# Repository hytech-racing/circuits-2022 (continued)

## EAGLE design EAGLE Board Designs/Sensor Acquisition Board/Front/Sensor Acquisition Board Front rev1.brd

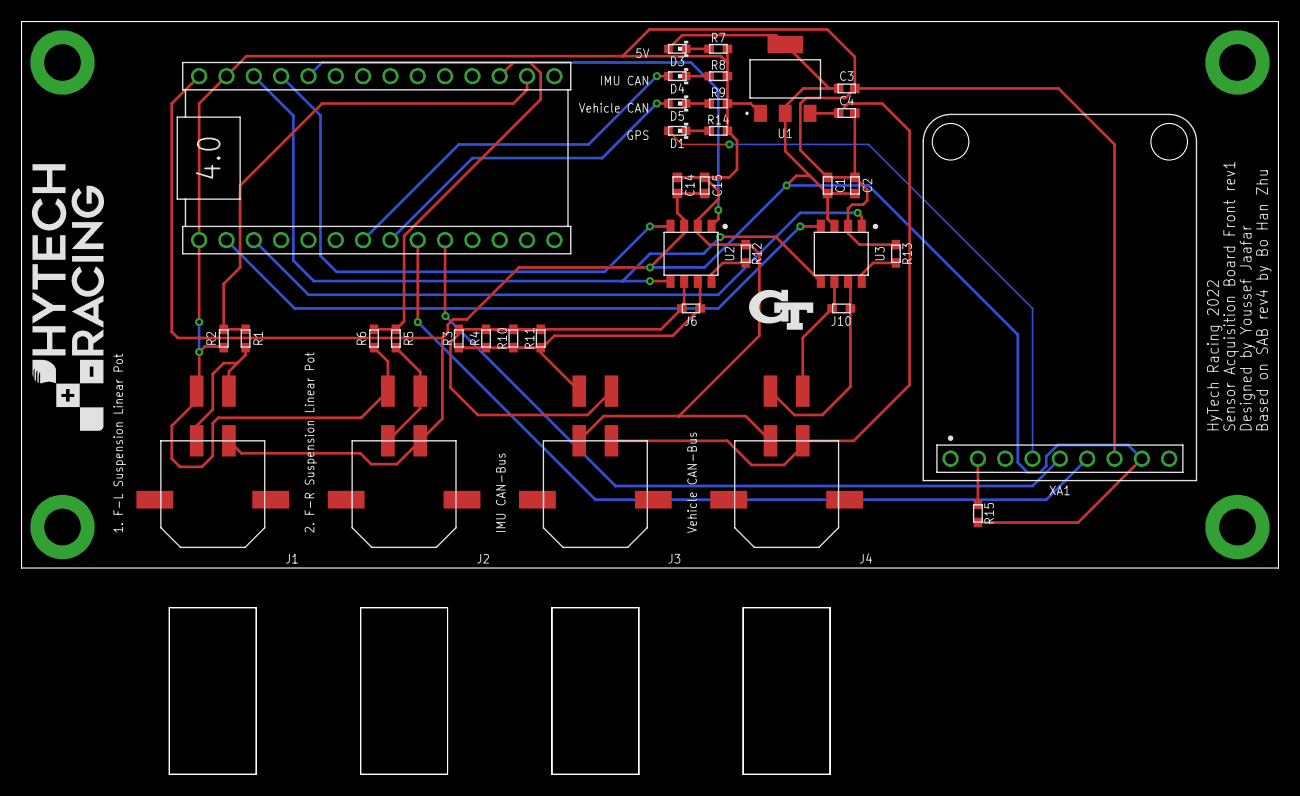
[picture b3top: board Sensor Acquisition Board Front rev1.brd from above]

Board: 2 copper layers, 116.8 x 50.8 mm, 42 parts (0 on the bottom side), 28 nets.

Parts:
A2: TEENSY_4.0; TEENSY_SHORT
C1, C15: CAPACITOR_0603_10V_0.1UF; 0603-CAP
C2, C14: CAPACITOR_0603_10V_1UF; 0603-CAP
C3: CAPACITOR_0603_10V_4.7UF; 0603-CAP
C4: CAPACITOR_0603_25V_1UF; 0603-CAP
D1, D3, D4, D5: LED_0603_RED; 0603-LED
J1, J2: CONNECTOR-4_μF_S_RA_; MOLEX_MICROFIT_SMD_RIGHTANGLE_04_DUAL
J3, J4: CONNECTOR-CAN_μF_S_RA_; MOLEX_MICROFIT_SMD_RIGHTANGLE_04_DUAL
J6, J10: JUMPER_0603_; 0603-RES
R1, R5, R12, R13, R15: RESISTOR_0603_10K; 0603-RES
R2, R6: RESISTOR_0603_12K; 0603-RES
R3, R4, R10, R11: RESISTOR_0603_240; 0603-RES
R7: RESISTOR_0603_1K; 0603-RES
R8, R9, R14: RESISTOR_0603_470; 0603-RES
U1: VOLTAGE_REGULATOR_SOT-223_5V; SOT-223
U2, U3: MCP2562FD; SOIC-08(NARROW,0.15")
U$1, U$2, U$4, U$5: MOUNTING_M3
U$6: LOGO_GT_0.25"
U$7: LOGO_HYTECH_MEDIUM
XA1: ULTIMATE_GPS

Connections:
+5V: A2.VIN, C1.2, C2.2, C3.1, C14.2, C15.2, D3.2, J1.1, J2.1, R15.2, U1.2, U1.4, U2.3, U3.3, XA1.VIN
+12V: C4.1, J3.1, J4.1, U1.3
CAN1_LED: A2.D5, D4.2
CAN2_LED: A2.D6, D5.2
CANH: J4.4, J10.1, U3.7
CANH1: J3.4, J6.1, R3.1, R4.1, R10.1, R11.1, U2.7
CANL: J4.3, J10.2, U3.6
CANL1: J3.3, J6.2, R3.2, R4.2, R10.2, R11.2, U2.6
CANRX1: A2.D23, U2.4
CANRX2: A2.D0, U3.4
CANTX1: A2.D22, U2.1
CANTX2: A2.D1, U3.1
GND: A2.AGND/GND, A2.GND, C1.1, C2.1, C3.2, C4.2, C14.1, C15.1, J1.4, J2.4, J3.2, J4.2, R2.1, R6.1, R7.2, R8.2, R9.2, R12.1, R13.1, R14.2, U1.1, U2.2, U3.2, XA1.GND
GPS_LED: D1.2, XA1.FIX
GPS_RX: A2.D7, XA1.RX
GPS_TX: A2.D8, XA1.TX
unnamed: R12.2, U2.8
unnamed: R13.2, U3.8
unnamed: D3.1, R7.1
unnamed: D1.1, R14.1
unnamed: D4.1, R8.1
unnamed: D5.1, R9.1
unnamed: R15.1, XA1.EN
unnamed: J1.2, J1.3, R1.2
unnamed: J2.2, J2.3, R5.2
SENSOR_1: A2.D14, R1.1, R2.2
SENSOR_2: A2.D15, R5.1, R6.2
TEENSY_3.3V: A2.3.3V, U2.5, U3.5

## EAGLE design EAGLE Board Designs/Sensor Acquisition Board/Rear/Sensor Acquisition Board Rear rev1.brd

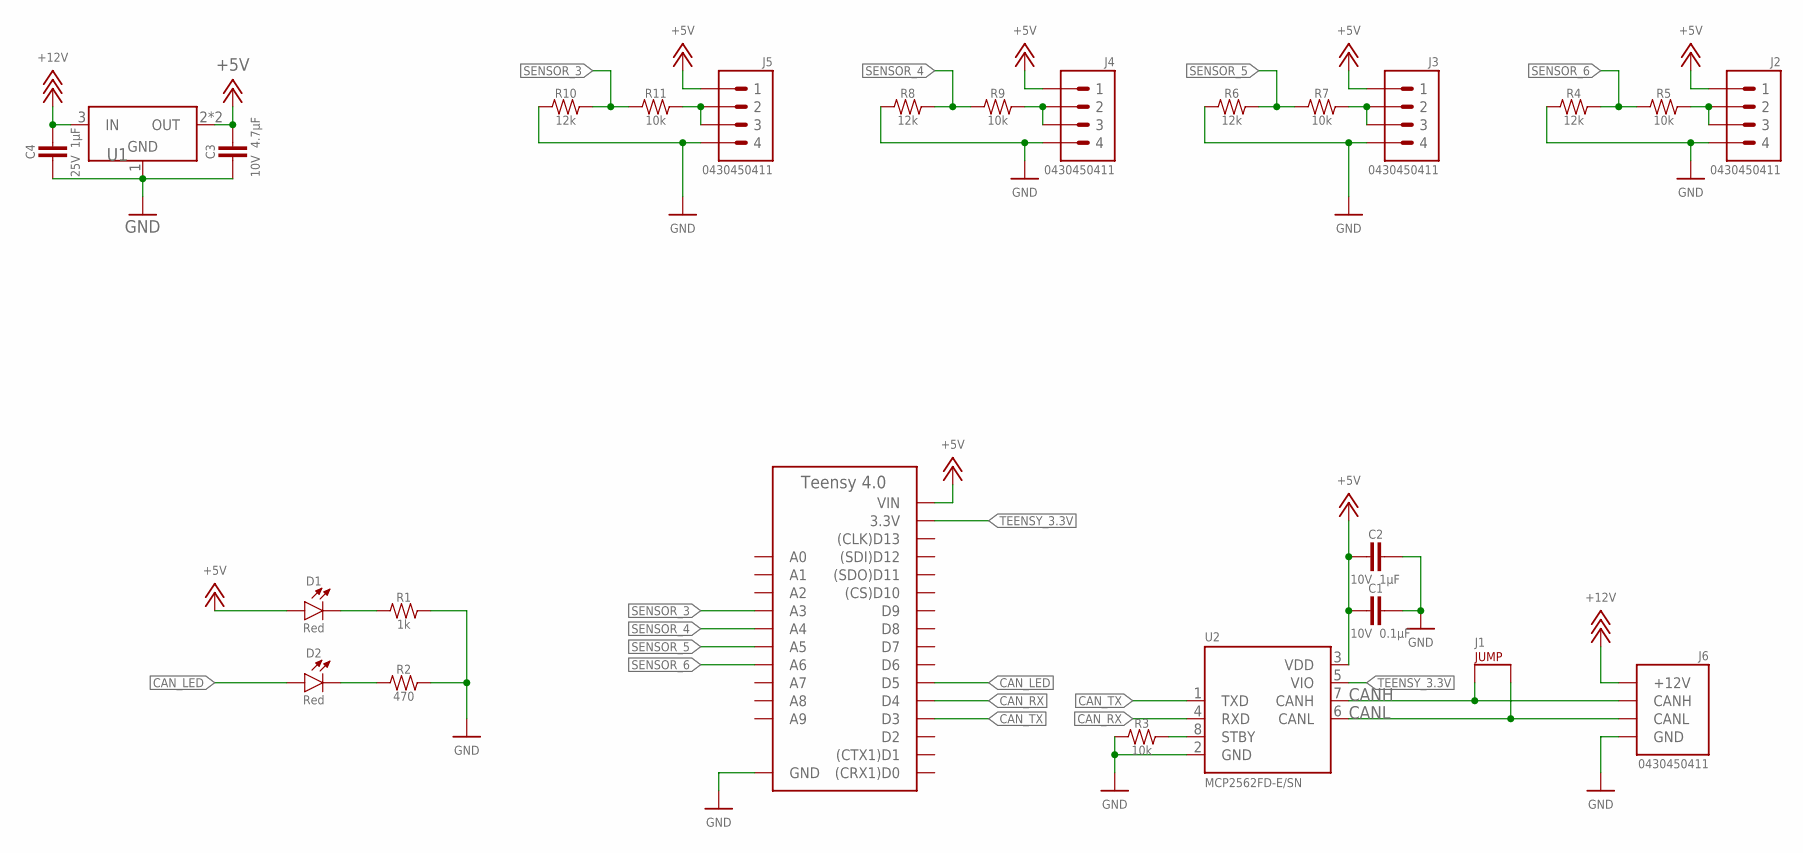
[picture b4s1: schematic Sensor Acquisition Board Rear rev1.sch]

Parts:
A1: TEENSY_4.0; TEENSY_SHORT
C1: CAPACITOR_0603_10V_0.1UF; 0603-CAP
C2: CAPACITOR_0603_10V_1UF; 0603-CAP
C3: CAPACITOR_0603_10V_4.7UF; 0603-CAP
C4: CAPACITOR_0603_25V_1UF; 0603-CAP
D1, D2: LED_0603_RED; 0603-LED
J1: JUMPER_0603_; 0603-RES
J2, J3, J4, J5: CONNECTOR-4_μF_S_RA_; MOLEX_MICROFIT_SMD_RIGHTANGLE_04_DUAL
J6: CONNECTOR-CAN_μF_S_RA_; MOLEX_MICROFIT_SMD_RIGHTANGLE_04_DUAL
R1: RESISTOR_0603_1K; 0603-RES
R2: RESISTOR_0603_470; 0603-RES
R3, R5, R7, R9, R11: RESISTOR_0603_10K; 0603-RES
R4, R6, R8, R10: RESISTOR_0603_12K; 0603-RES
U1: VOLTAGE_REGULATOR_SOT-223_5V; SOT-223
U2: MCP2562FD; SOIC-08(NARROW,0.15")

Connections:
+5V: A1.VIN, C1.2, C2.2, C3.1, D1.2 (A), J2.1, J3.1, J4.1, J5.1, U1.2 (OUT), U1.4 (OUT), U2.3 (VDD)
+12V: C4.1, J6.1 (+12V), U1.3 (IN)
CANH: J1.1, J6.4 (CANH), U2.7 (CANH)
CANL: J1.2, J6.3 (CANL), U2.6 (CANL)
CAN_LED: A1.D5, D2.2 (A)
CAN_RX: A1.D4, U2.4 (RXD)
CAN_TX: A1.D3, U2.1 (TXD)
unnamed: D1.1 (C), R1.1
unnamed: D2.1 (C), R2.1
unnamed: R3.2, U2.8 (STBY)
unnamed: J2.2, J2.3, R5.2
unnamed: J4.2, J4.3, R9.2
unnamed: J3.2, J3.3, R7.2
unnamed: J5.2, J5.3, R11.2
SENSOR_3: A1.D17 (A3), R10.2, R11.1
SENSOR_4: A1.D18 (A4), R8.2, R9.1
SENSOR_5: A1.D19 (A5), R6.2, R7.1
SENSOR_6: A1.D20 (A6), R4.2, R5.1
TEENSY_3.3V: A1.3.3V, U2.5 (VIO)

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
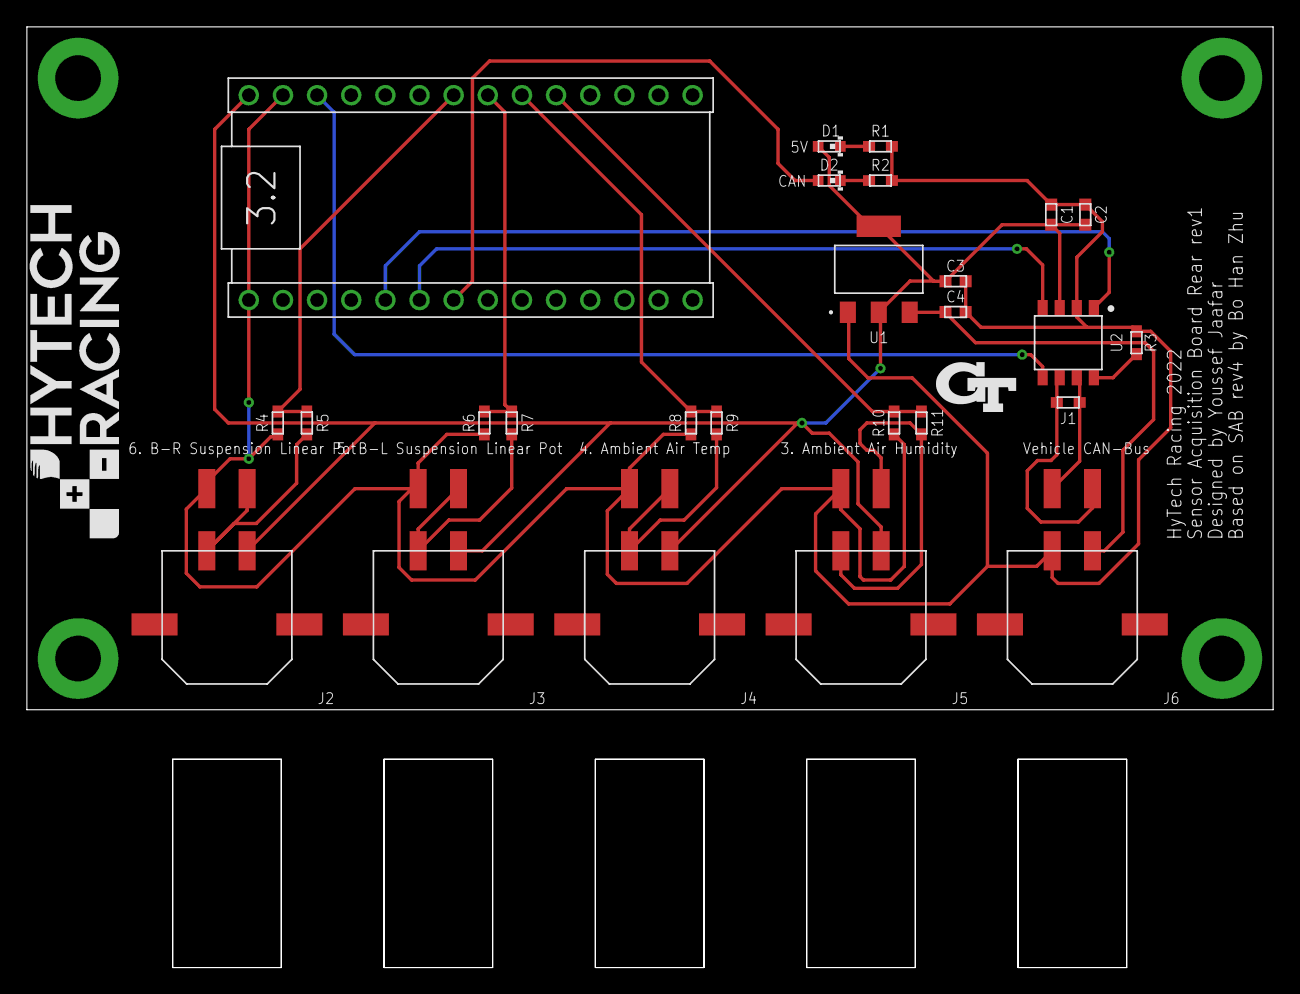
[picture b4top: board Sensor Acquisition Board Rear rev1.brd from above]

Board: 2 copper layers, 92.7 x 50.8 mm, 32 parts (0 on the bottom side), 20 nets.

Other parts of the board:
$$U$6: MOUNTING_M3
U$1, U$2, U$5: MOUNTING_M3
U$3: LOGO_GT_0.25"
U$4: LOGO_HYTECH_MEDIUM

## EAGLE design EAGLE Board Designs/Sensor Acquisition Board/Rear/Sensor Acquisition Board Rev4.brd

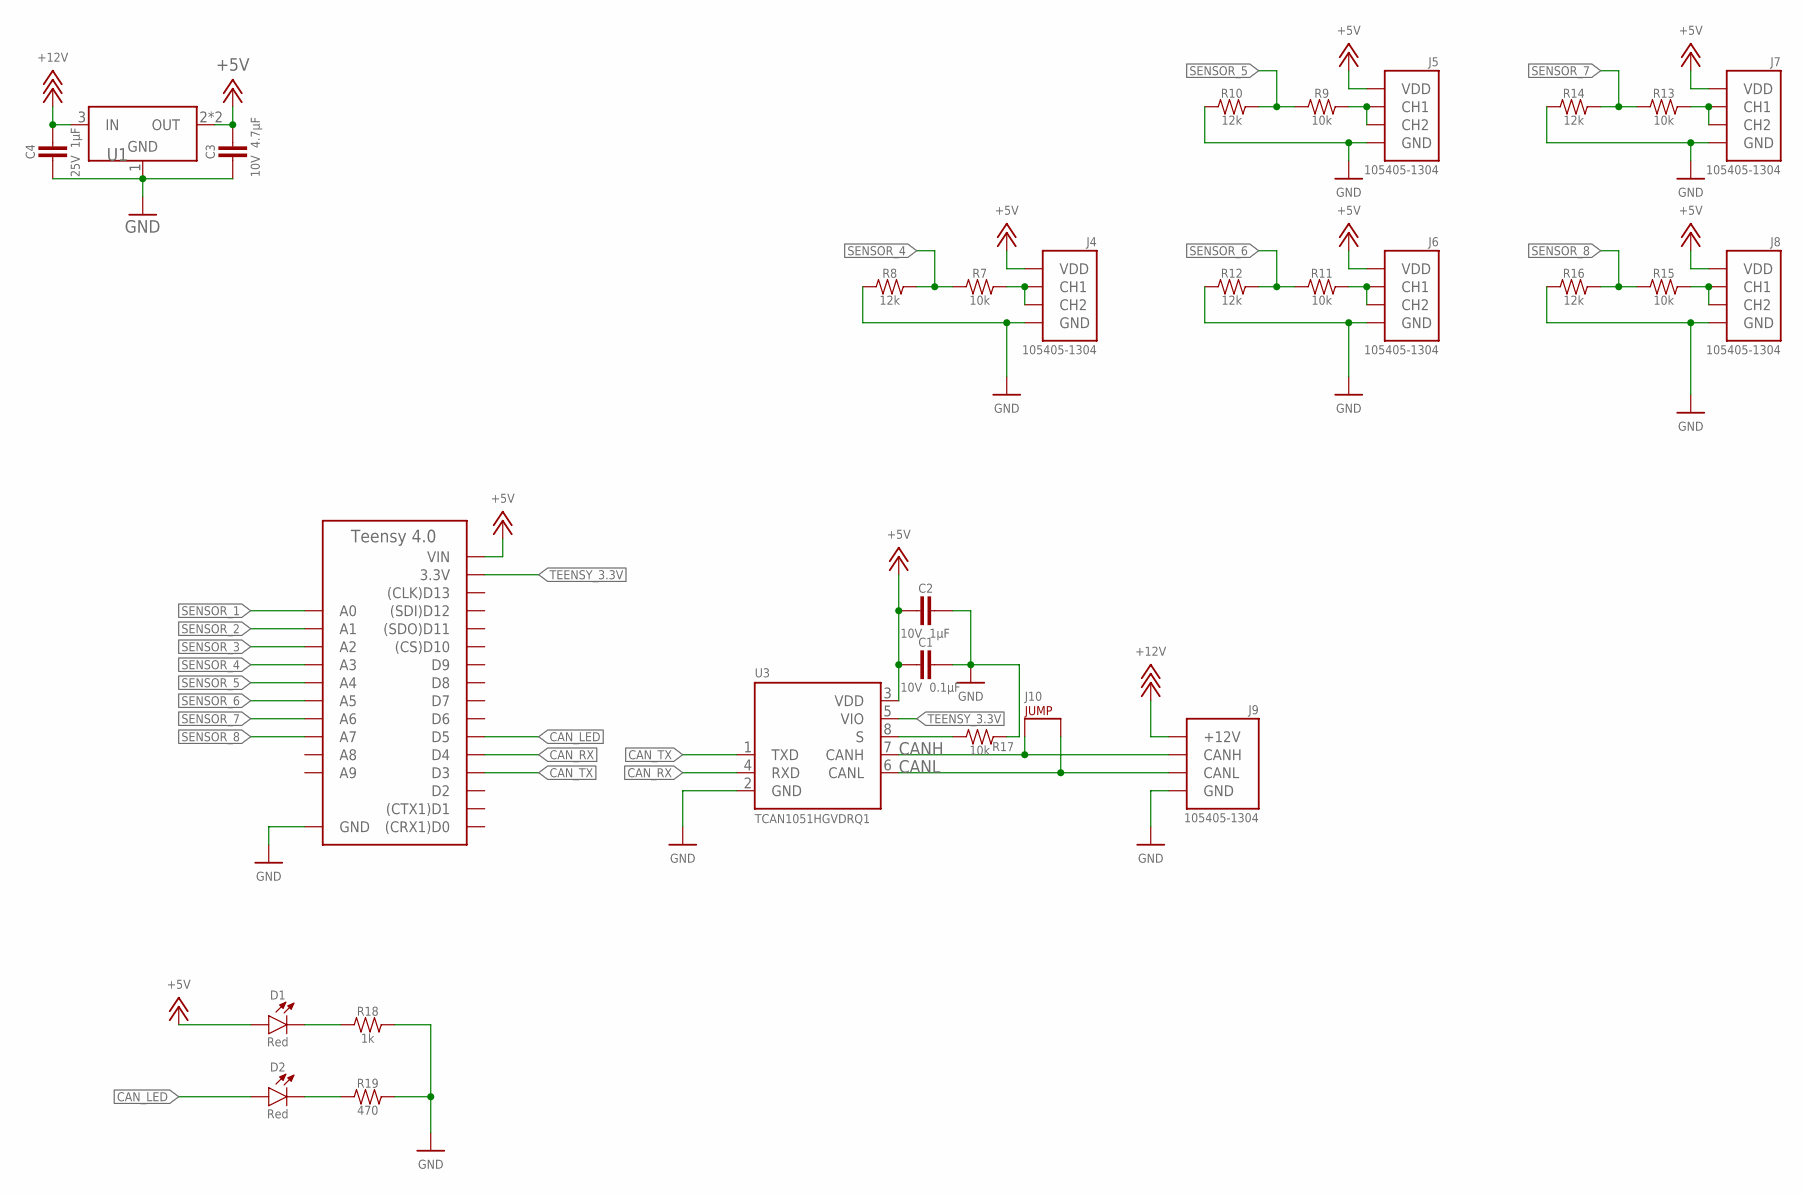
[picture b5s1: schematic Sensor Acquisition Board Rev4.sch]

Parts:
A2: TEENSY_4.0; TEENSY_SHORT
C1: CAPACITOR_0603_10V_0.1UF; 0603-CAP
C2: CAPACITOR_0603_10V_1UF; 0603-CAP
C3: CAPACITOR_0603_10V_4.7UF; 0603-CAP
C4: CAPACITOR_0603_25V_1UF; 0603-CAP
D1, D2: LED_0603_RED; 0603-LED
J4, J5, J6, J7, J8: CONNECTOR-SENSOR_NF_S_RA_BLACK; MOLEX_NANOFIT_SMD_RIGHTANGLE_04
J9: CONNECTOR-CAN_NF_S_RA_BLACK; MOLEX_NANOFIT_SMD_RIGHTANGLE_04
J10: JUMPER_0603_; 0603-RES
R7, R9, R11, R13, R15, R17: RESISTOR_0603_10K; 0603-RES
R8, R10, R12, R14, R16: RESISTOR_0603_12K; 0603-RES
R18: RESISTOR_0603_1K; 0603-RES
R19: RESISTOR_0603_470; 0603-RES
U1: VOLTAGE_REGULATOR_SOT-223_5V; SOT-223
U3: TCAN1051HQV-Q1; SOIC-08(NARROW,0.15")

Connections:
+5V: A2.VIN, C1.2, C2.2, C3.1, D1.2 (A), J4.1 (VDD), J5.1 (VDD), J6.1 (VDD), J7.1 (VDD), J8.1 (VDD), U1.2 (OUT), U1.4 (OUT), U3.3 (VDD)
+12V: C4.1, J9.1 (+12V), U1.3 (IN)
CANH: J9.4 (CANH), J10.1, U3.7 (CANH)
CANL: J9.3 (CANL), J10.2, U3.6 (CANL)
CAN_LED: A2.D5, D2.2 (A)
CAN_RX: A2.D4, U3.4 (RXD)
CAN_TX: A2.D3, U3.1 (TXD)
GND: A2.AGND/GND (GND), A2.GND, C1.1, C2.1, C3.2, C4.2, J4.2 (GND), J5.2 (GND), J6.2 (GND), J7.2 (GND), J8.2 (GND), J9.2 (GND), R8.1, R10.1, R12.1, R14.1, R16.1, R17.2, R18.2, R19.2, U1.1 (GND), U3.2 (GND)
unnamed: D1.1 (C), R18.1
unnamed: D2.1 (C), R19.1
unnamed: J8.3 (CH1), J8.4 (CH2), R15.2
unnamed: R17.1, U3.8 (S)
unnamed: J7.3 (CH1), J7.4 (CH2), R13.2
unnamed: J5.3 (CH1), J5.4 (CH2), R9.2
unnamed: J6.3 (CH1), J6.4 (CH2), R11.2
unnamed: J4.3 (CH1), J4.4 (CH2), R7.2
SENSOR_1: A2.D14 (A0)
SENSOR_2: A2.D15 (A1)
SENSOR_3: A2.D16 (A2)
SENSOR_4: A2.D17 (A3), R7.1, R8.2
SENSOR_5: A2.D18 (A4), R9.1, R10.2
SENSOR_6: A2.D19 (A5), R11.1, R12.2
SENSOR_7: A2.D20 (A6), R13.1, R14.2
SENSOR_8: A2.D21 (A7), R15.1, R16.2
TEENSY_3.3V: A2.3.3V, U3.5 (VIO)

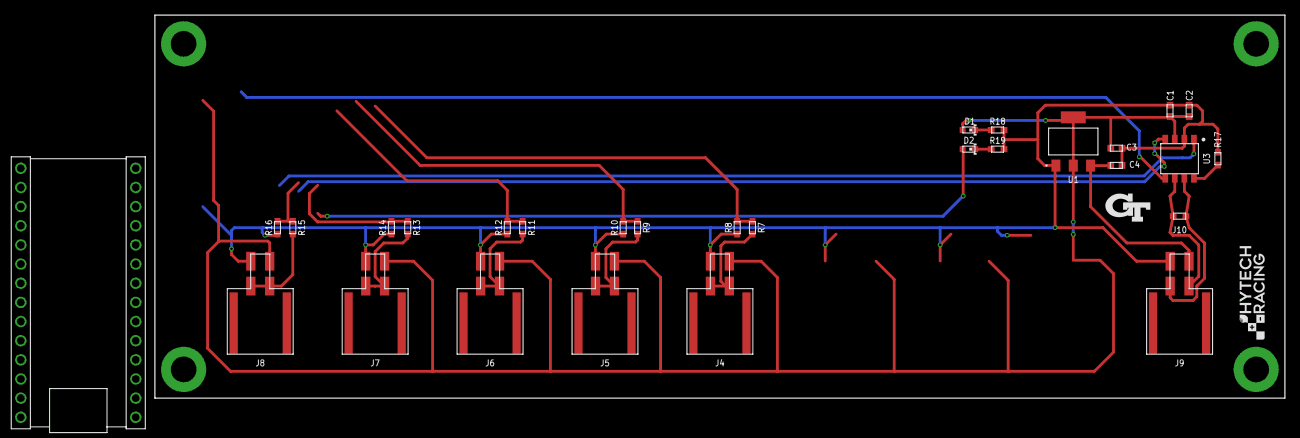
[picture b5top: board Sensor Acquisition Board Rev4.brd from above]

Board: 2 copper layers, 149.9 x 50.8 mm, 35 parts (0 on the bottom side), 22 nets.

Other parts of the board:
U$1, U$2, U$4, U$5: MOUNTING_M3
U$3: LOGO_HYTECH_0.5"
U$6: LOGO_GT_0.25"

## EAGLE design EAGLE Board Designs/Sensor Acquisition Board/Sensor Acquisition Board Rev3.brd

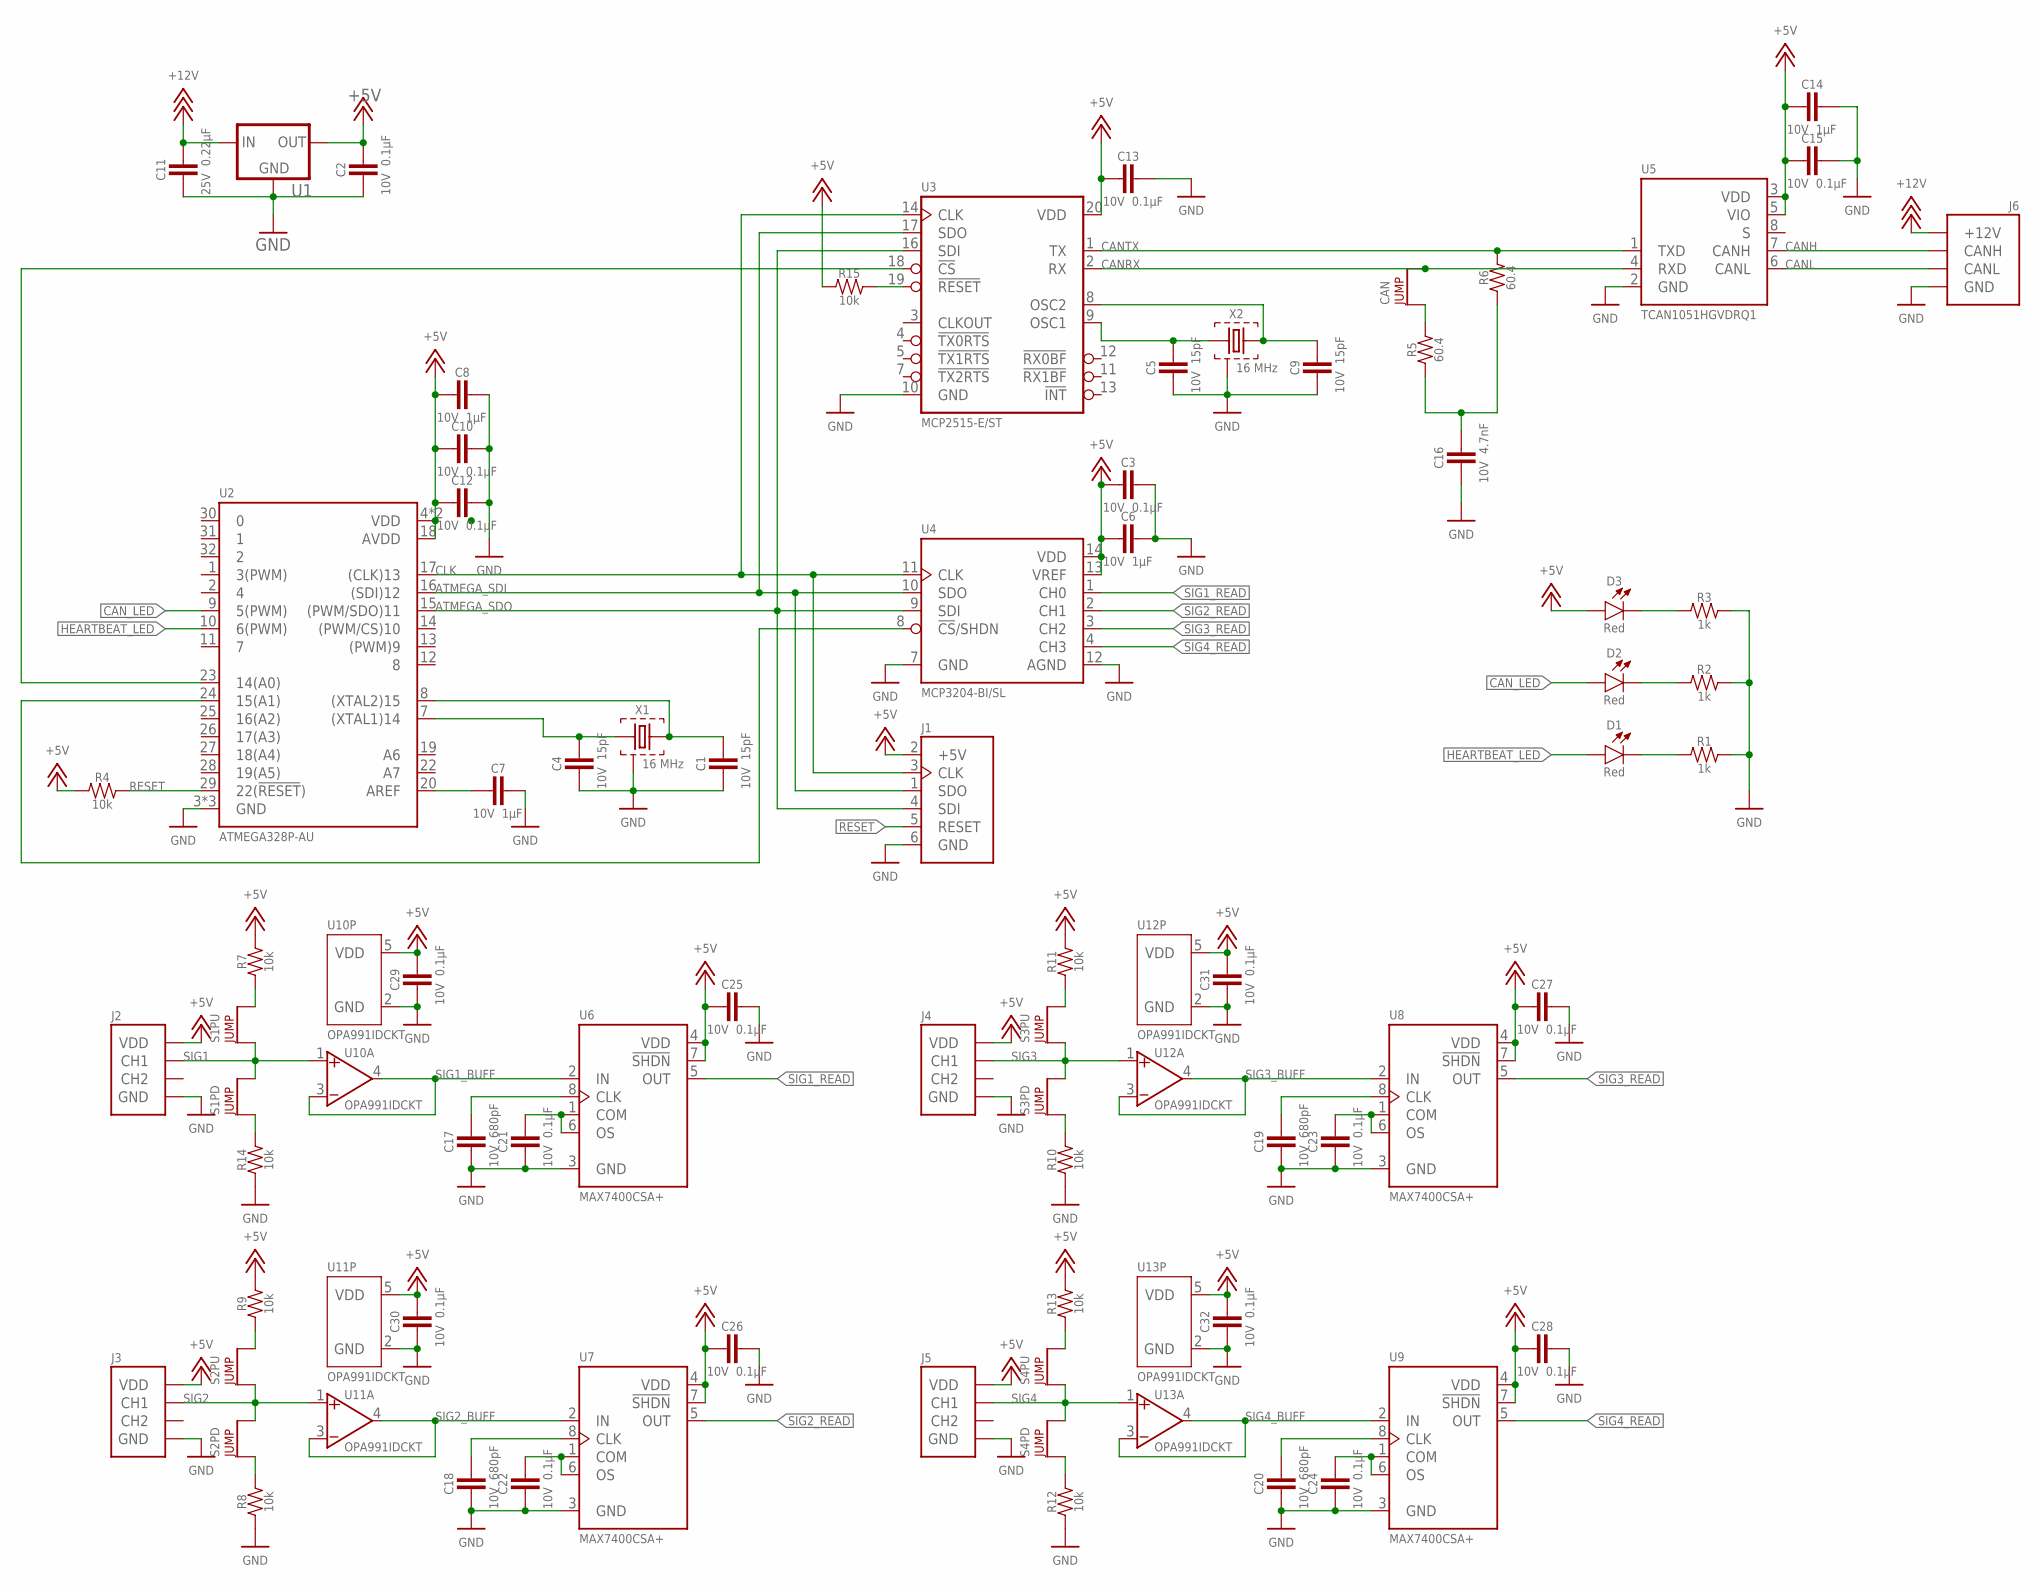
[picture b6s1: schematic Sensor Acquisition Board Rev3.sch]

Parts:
C1, C4, C5, C9: CAPACITOR_0603_10V_15PF; 0603-CAP
C2, C3, C10, C12, C13, C15, C21, C22, C23, C24, C25, C26, C27, C28, C29, C30, C31, C32: CAPACITOR_0603_10V_0.1UF; 0603-CAP
C6, C7, C8, C14: CAPACITOR_0603_10V_1UF; 0603-CAP
C11: CAPACITOR_0603_25V_0.22UF; 0603-CAP
C16: CAPACITOR_0603_10V_4.7NF; 0603-CAP
C17, C18, C19, C20: CAPACITOR_0603_10V_680PF; 0603-CAP
CAN: JUMPER_1X02_; 1X02
D1, D2, D3: LED_0603_RED; 0603-LED
J1: CONNECTOR-AVR-ISP__; 2X03
J2, J3, J4, J5: CONNECTOR-SENSOR_NF_S_RA_BLACK; MOLEX_NANOFIT_SMD_RIGHTANGLE_04
J6: CONNECTOR-CAN_NF_S_RA_BLACK; MOLEX_NANOFIT_SMD_RIGHTANGLE_04
R1, R2, R3: RESISTOR_0603_1K; 0603-RES
R4, R7, R8, R9, R10, R11, R12, R13, R14, R15: RESISTOR_0603_10K; 0603-RES
R5, R6: RESISTOR_0603_60.4; 0603-RES
S1PD, S1PU, S2PD, S2PU, S3PD, S3PU, S4PD, S4PU: JUMPER_1X02_; 1X02
U1: LM340; SOT223
U2: ATMEGA328P-AU; TQFP-32
U3: MCP2515; TSSOP-20
U4: MCP3204; SOIC-14
U5: CAN_TRANSCIEVER_TCAN1051HQV-Q1; SOIC-08
U6, U7, U8, U9: MAX7400; SOIC-08(NARROW,0.15")
U10, U11, U12, U13: OPAMP_1_CHANNEL_OPA991; SC-70-5
X1, X2: CRYSTAL16MHZ; ABM3B

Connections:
+5V: C2.1, C3.2, C6.2, C8.2, C10.2, C12.2, C13.2, C14.2, C15.2, C25.2, C26.2, C27.2, C28.2, C29.1, C30.1, C31.1, C32.1, D3.2 (A), J1.2 (+5V), J2.1 (VDD), J3.1 (VDD), J4.1 (VDD), J5.1 (VDD), R4.1, R7.2, R9.2, R11.2, R13.2, R15.1, U1.3 (OUT), U2.4 (VDD), U2.6 (VDD), U2.18 (AVDD), U3.20 (VDD), U4.13 (VREF), U4.14 (VDD), U5.3 (VDD), U5.5 (VIO), U6.4 (VDD), U6.7 (!SHDN), U7.4 (VDD), U7.7 (!SHDN), U8.4 (VDD), U8.7 (!SHDN), U9.4 (VDD), U9.7 (!SHDN), U10.5 (VDD), U11.5 (VDD), U12.5 (VDD), U13.5 (VDD)
+12V: C11.1, J6.1 (+12V), U1.1 (IN)
ATMEGA_CS: U2.24 (15(A1)), U4.8 (!CS!/SHDN)
ATMEGA_SDI: J1.1 (SDO), U2.16 ((SDI)12), U3.17 (SDO), U4.10 (SDO)
ATMEGA_SDO: J1.4 (SDI), U2.15 ((PWM/SDO)11), U3.16 (SDI), U4.9 (SDI)
CANH: J6.4 (CANH), U5.7 (CANH)
CANL: J6.3 (CANL), U5.6 (CANL)
CANRX: CAN.2, U3.2 (RX), U5.4 (RXD)
CANTX: R6.2, U3.1 (TX), U5.1 (TXD)
CAN_LED: D2.2 (A), U2.9 (5(PWM))
CLK: J1.3 (CLK), U2.17 ((CLK)13), U3.14 (CLK), U4.11 (CLK)
GND: C1.2, C2.2, C3.1, C4.2, C5.2, C6.1, C7.1, C8.1, C9.2, C10.1, C11.2, C12.1, C13.1, C14.1, C15.1, C16.2, C17.2, C18.2, C19.2, C20.2, C21.2, C22.2, C23.2, C24.2, C25.1, C26.1, C27.1, C28.1, C29.2, C30.2, C31.2, C32.2, J1.6 (GND), J2.2 (GND), J3.2 (GND), J4.2 (GND), J5.2 (GND), J6.2 (GND), R1.2, R2.2, R3.2, R8.1, R10.1, R12.1, R14.1, U1.2 (GND), U1.4 (GND), U2.3 (GND), U2.5 (GND), U2.21 (GND), U3.10 (GND), U4.7 (GND), U4.12 (AGND), U5.2 (GND), U6.3 (GND), U7.3 (GND), U8.3 (GND), U9.3 (GND), U10.2 (GND), U11.2 (GND), U12.2 (GND), U13.2 (GND), X1.2 (GND), X1.4 (GND), X2.2 (GND), X2.4 (GND)
HEARTBEAT_LED: D1.2 (A), U2.10 (6(PWM))
unnamed: CAN.1, R5.2
unnamed: C16.1, R5.1, R6.1
unnamed: C17.1, U6.8 (CLK)
unnamed: C21.1, U6.1 (COM), U6.6 (OS)
unnamed: R15.2, U3.19 (!RESET)
unnamed: D3.1 (C), R3.1
unnamed: D2.1 (C), R2.1
unnamed: D1.1 (C), R1.1
unnamed: U2.23 (14(A0)), U3.18 (!CS)
unnamed: C5.1, U3.9 (OSC1), X2.1
unnamed: C9.1, U3.8 (OSC2), X2.3
unnamed: C4.1, U2.7 ((XTAL1)14), X1.1
unnamed: C1.1, U2.8 ((XTAL2)15), X1.3
unnamed: C7.2, U2.20 (AREF)
unnamed: R7.1, S1PU.2
unnamed: R14.2, S1PD.1
unnamed: C18.1, U7.8 (CLK)
unnamed: C22.1, U7.1 (COM), U7.6 (OS)
unnamed: R9.1, S2PU.2
unnamed: R8.2, S2PD.1
unnamed: C19.1, U8.8 (CLK)
unnamed: C23.1, U8.1 (COM), U8.6 (OS)
unnamed: R11.1, S3PU.2
unnamed: R10.2, S3PD.1
unnamed: C20.1, U9.8 (CLK)
unnamed: C24.1, U9.1 (COM), U9.6 (OS)
unnamed: R13.1, S4PU.2
unnamed: R12.2, S4PD.1
RESET: J1.5 (RESET), R4.2, U2.29 (22(!RESET!))
SIG1: J2.3 (CH1), S1PD.2, S1PU.1, U10.1 (VIN+)
SIG1_BUFF: U6.2 (IN), U10.3 (VIN-), U10.4 (VOUT)
SIG1_READ: U4.1 (CH0), U6.5 (OUT)
SIG2: J3.3 (CH1), S2PD.2, S2PU.1, U11.1 (VIN+)
SIG2_BUFF: U7.2 (IN), U11.3 (VIN-), U11.4 (VOUT)
SIG2_READ: U4.2 (CH1), U7.5 (OUT)
SIG3: J4.3 (CH1), S3PD.2, S3PU.1, U12.1 (VIN+)
SIG3_BUFF: U8.2 (IN), U12.3 (VIN-), U12.4 (VOUT)
SIG3_READ: U4.3 (CH2), U8.5 (OUT)
SIG4: J5.3 (CH1), S4PD.2, S4PU.1, U13.1 (VIN+)
SIG4_BUFF: U9.2 (IN), U13.3 (VIN-), U13.4 (VOUT)
SIG4_READ: U4.4 (CH3), U9.5 (OUT)

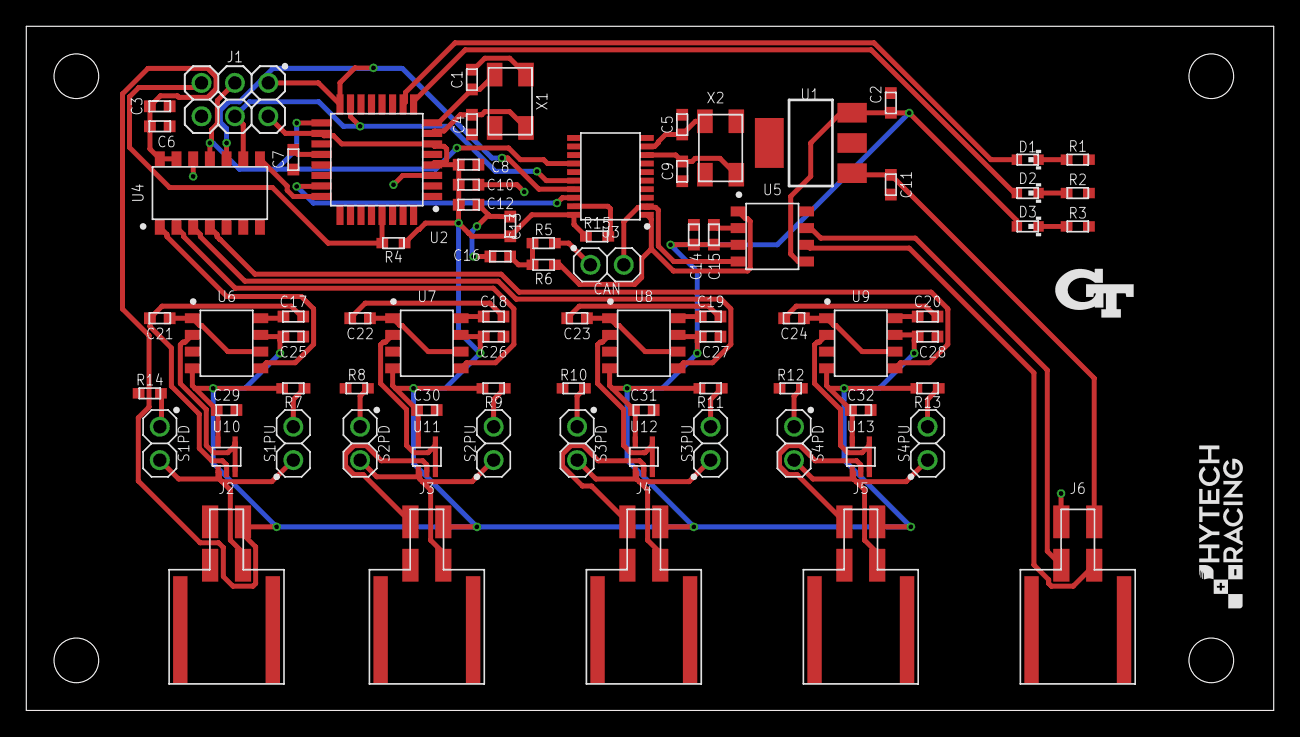
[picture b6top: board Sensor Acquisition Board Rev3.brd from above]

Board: 2 copper layers, 94.9 x 52.1 mm, 86 parts (0 on the bottom side), 54 nets.

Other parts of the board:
U$1, U$2, U$4, U$5: MOUNTING_M3
U$3: LOGO_HYTECH_0.5"
U$6: LOGO_GT_0.25"

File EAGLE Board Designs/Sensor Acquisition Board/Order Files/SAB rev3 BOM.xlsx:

Qty | Value | Device | Package | Parts | Description | CAPACITANCE | COLOR | DKPN | FREQUENCY | LOAD_CAPACITANCE | MANUFACTURER | MOPN | MPN | POWER | RESISTANCE | SHUNT_CAPACITANCE | TOLERANCE | VOLTAGE | VOLTAGE_CONTINUOUS | VOLTAGE_MAX | Column1
1 | ATMEGA328P-AU | ATMEGA328P-AU | TQFP-32 | U2 | ATmega328P |  |  | ATMEGA328P-AURCT-ND |  |  | Microchip Technology | 556-ATMEGA328P-AU | ATMEGA328P-AU
1 | CAN_TRANSCIEVER_TCAN1051HQV-Q1 | CAN_TRANSCIEVER_TCAN1051HQV-Q1 | SOIC-08 | U5 | TCAN1051*V Can Tranciever |  |  | 296-49935-1-ND |  |  | Texas Instruments | 595-TCAN1051HGVDQ1 | TCAN1051HGVDRQ1
18 | CAPACITOR_0603_10V_0.1UF | CAPACITOR_0603_10V_0.1UF | 0603-CAP | C2, C3, C10, C12, C13, C15, C21, C22, C23, C24, C25, C26, C27, C28, C29, C30, C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 | Capacitor, Non-Polarized | 0.1ÂµF |  | 720-1688-1-ND |  |  | Vishay Vitramon | 77-VJ0603Y104JXQPBC | VJ0603Y104JXQPW1BC |  |  |  | 0.05 | 10V
4 | CAPACITOR_0603_10V_15PF | CAPACITOR_0603_10V_15PF | 0603-CAP | C1, C4, C5, C9 | Capacitor, Non-Polarized | 15pF |  | 720-VJ0603A150FXQPW1BCCT-ND |  |  | Vishay Vitramon | 77-VJ0603A150FXQPBC | VJ0603A150FXQPW1BC |  |  |  | 0.01 | 10V
4 | CAPACITOR_0603_10V_1UF | CAPACITOR_0603_10V_1UF | 0603-CAP | C6, C7, C8, C14 | Capacitor, Non-Polarized | 1ÂµF |  | 311-1796-1-ND |  |  | Yageo | 603-CC603KRX7R6BB105 | CC0603KRX7R6BB105 |  |  |  | 0.1 | 10V
1 | CAPACITOR_0603_10V_4.7NF | CAPACITOR_0603_10V_4.7NF | 0603-CAP | C16 | Capacitor, Non-Polarized | 4.7nF |  | 732-7931-1-ND |  |  | WÃ¼rth Elektronik | 710-885012206012 | 885012206012 |  |  |  | 0.1 | 10V
4 | CAPACITOR_0603_10V_680PF | CAPACITOR_0603_10V_680PF | 0603-CAP | C17, C18, C19, C20 | Capacitor, Non-Polarized | 680pF |  | 732-7757-1-ND |  |  | WÃ¼rth Elektronik | 710-885012006013 | 885012006013 |  |  |  | 0.05 | 10V
1 | CAPACITOR_0603_25V_0.22UF | CAPACITOR_0603_25V_0.22UF | 0603-CAP | C11 | Capacitor, Non-Polarized | 0.22ÂµF |  | 1292-1420-1-ND |  |  | Walsin Technology Corporation | 791-0603B224K250CT | 0603B224K250CT |  |  |  | 0.1 | 25V
1 | CONNECTOR-AVR-ISP__ | CONNECTOR-AVR-ISP__ | 2X03 | J1 | AVR ISP 6-pin Header |  |  | S2011EC-03-ND
1 | CONNECTOR-CAN_NF_S_RA_BLACK | CONNECTOR-CAN_NF_S_RA_BLACK | MOLEX_NANOFIT_SMD_RIGHTANGLE_04 | J6 | HyTech CAN Connector |  |  |  |  |  | Molex |  | 105405-1304
4 | CONNECTOR-SENSOR_NF_S_RA_BLACK | CONNECTOR-SENSOR_NF_S_RA_BLACK | MOLEX_NANOFIT_SMD_RIGHTANGLE_04 | J2, J3, J4, J5 | HyTech Sensor Connector |  |  |  |  |  | Molex |  | 105405-1304
2 | CRYSTAL16MHZ | CRYSTAL16MHZ | ABM3B | X1, X2 | Crystal |  |  | 887-1298-1-ND | 16 MHz | 10pF | TXC CORPORATION | 717-7B-16.000MEEQ-T | 7B-16.000MEEQ-T |  |  | 2 - 5 pF
9 | JUMPER_1X02_ | JUMPER_1X02_ | 1X02 | CAN, S1PD, S1PU, S2PD, S2PU, S3PD, S3PU, S4PD, S4PU | 2 Pin Connector
3 | LED_0603_RED | LED_0603_RED | 0603-LED | D1, D2, D3 | LED |  | Red | 754-1786-1-ND |  |  | Kingbright | 604-APT1608SECKJ3PRV | APT1608SECK/J3-PRV
1 | LM340 | LM340 | SOT223 | U1 | LM340
4 | MAX7400 | MAX7400 | SOIC-08(NARROW,0.15)" | U6, U7, U8, U9 | 8th-Order Maxim Filter |  |  | MAX7400CSA+-ND |  |  | Maxim Integrated | 700-MAX7400CSA | MAX7400CSA+
1 | MCP2515 | MCP2515 | TSSOP-20 | U3 | MCP2515 Can Controller |  |  | MCP2515-E/ST-ND |  |  | Microchip Technology | 579-MCP2515-E/ST | MCP2515-E/ST
1 | MCP3204 | MCP3204 | SOIC-14 | U4 | MCP3204 4-Channel ADC |  |  | MCP3204-BI/SL-ND |  |  | Microchip Technology | 579-MCP3204-BI/SL | MCP3204-BI/SL
4 | OPAMP_1_CHANNEL_OPA991 | OPAMP_1_CHANNEL_OPA991 | SC-70-5 | U10, U11, U12, U13 | Op-Amp 1 Channel |  |  |  |  |  |  |  | OPA991IDCKT
10 | RESISTOR_0603_10K | RESISTOR_0603_10K | 0603-RES | R4, R7, R8, R9, R10, R11, R12, R13, R14, R15 | Resistor |  |  | 311-10.0KHRCT-ND |  |  | Yageo | 603-RC0603FR-0710KL | RC0603FR-0710KL | 0.1W | 10k |  | 0.01 |  | 31.62V | 75V
3 | RESISTOR_0603_1K | RESISTOR_0603_1K | 0603-RES | R1, R2, R3 | Resistor |  |  | 311-1.00KHRCT-ND |  |  | Yageo | 603-RC0603FR-071KL | RC0603FR-071KL | 0.1W | 1k |  | 0.01 |  | 10.00V | 75V
2 | RESISTOR_0603_60.4 | RESISTOR_0603_60.4 | 0603-RES | R5, R6 | Resistor |  |  | 311-60.4HRCT-ND |  |  | Yageo | 603-RC0603FR-0760R4L | RC0603FR-0760R4L | 0.1W | 60.4 |  | 0.01 |  | 2.48V | 75V
